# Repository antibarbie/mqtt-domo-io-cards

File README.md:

# mqtt-domo-io-cards
Kicad project for I/O Cards - For DIN RAIL deployment in a domotic "Distribution board"

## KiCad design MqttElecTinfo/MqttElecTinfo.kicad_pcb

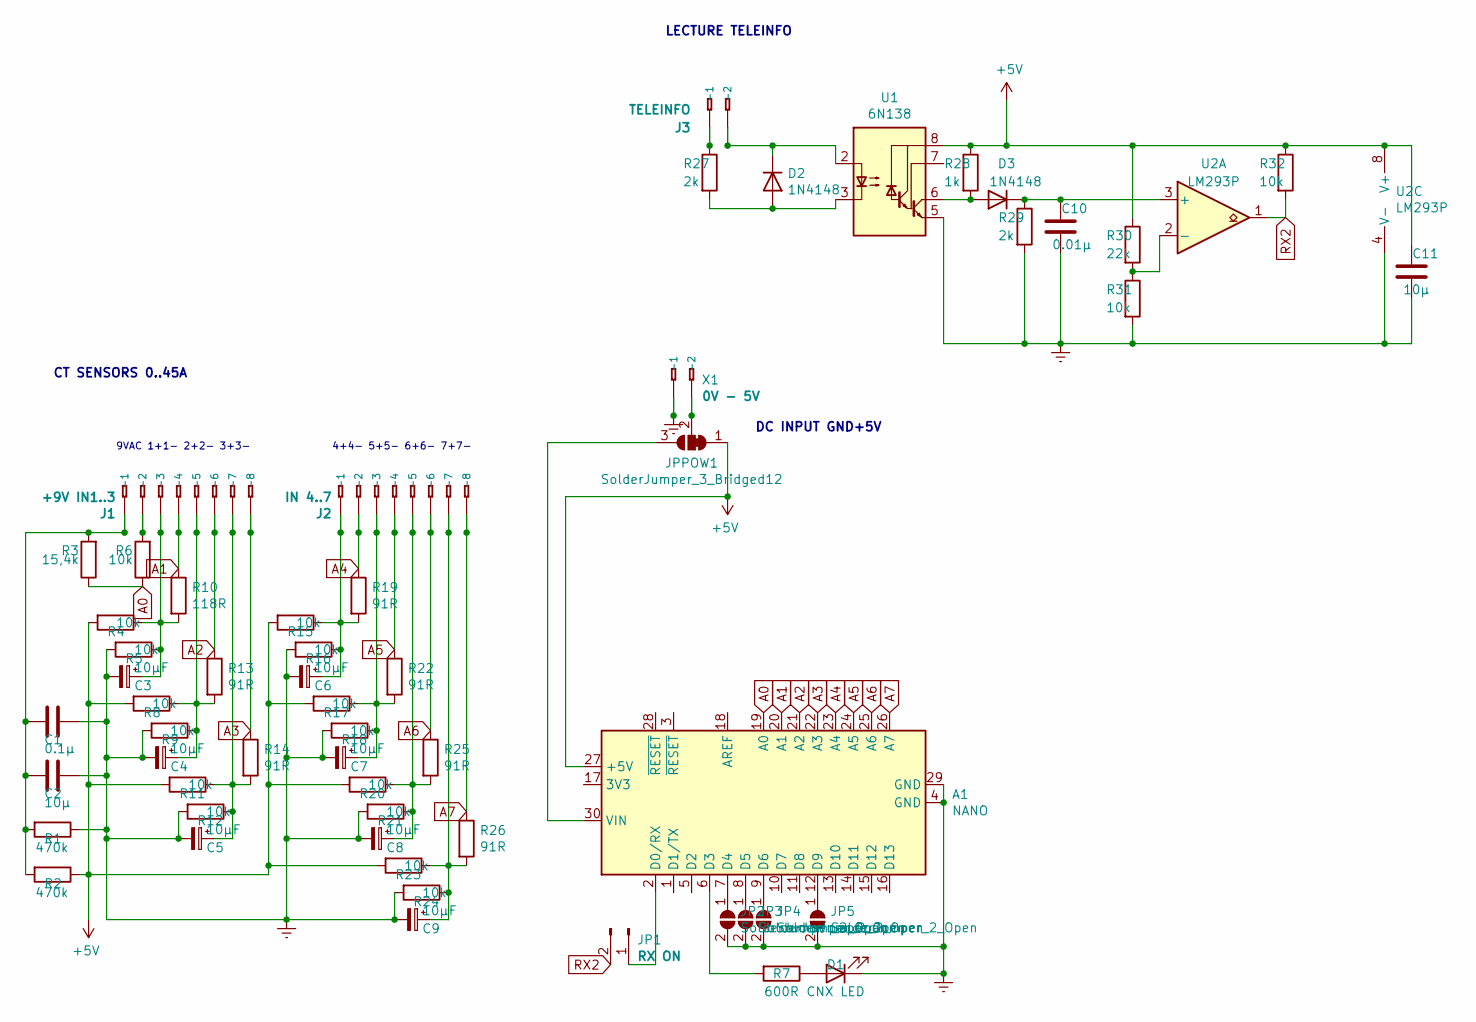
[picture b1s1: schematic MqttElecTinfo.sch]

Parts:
A1: NANO; Arduino_Nano
C1: 0.1µ; CP_Radial_Tantal_D4.5mm_P2.50mm
C2: 10µ; CP_Radial_Tantal_D4.5mm_P5.00mm
C3, C4, C5, C6, C7, C8, C9: 10µF; CP_Radial_D5.0mm_P2.50mm
C10: 0.01µ; CP_Radial_Tantal_D5.0mm_P2.50mm
C11: 10µ; CP_Radial_Tantal_D5.0mm_P5.00mm
D1: CNX LED; LED_D3.0mm
D2, D3: 1N4148; D_DO-35_SOD27_P7.62mm_Horizontal
J1: +9V IN1..3; 233-508; MPN 0233-0508
J2: IN 4..7; 233-508; MPN 0233-0508
J3: TELEINFO; 233-502; MPN 0233-0508
JP1: RX ON; PinHeader_1x02_P2.54mm_Vertical
JP2, JP3, JP4, JP5: SolderJumper_2_Open; SolderJumper-2_P1.3mm_Open_Pad1.0x1.5mm
JPPOW1: SolderJumper_3_Bridged12; SolderJumper-3_P1.3mm_Bridged2Bar12_Pad1.0x1.5mm_NumberLabe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
R1, R2: 470k; R_Axial_DIN0207_L6.3mm_D2.5mm_P2.54mm_Vertical
R3: 15,4k; R_Axial_DIN0207_L6.3mm_D2.5mm_P2.54mm_Vertical
R4, R5, R6, R8, R9, R11, R12, R15, R16, R17, R18, R20, R21, R23, R24, R31, R32: 10k; R_Axial_DIN0207_L6.3mm_D2.5mm_P2.54mm_Vertical
R7: 600R; R_Axial_DIN0207_L6.3mm_D2.5mm_P7.62mm_Horizontal
R10: 118R; R_Axial_DIN0207_L6.3mm_D2.5mm_P2.54mm_Vertical
R13, R14, R19, R22, R25, R26: 91R; R_Axial_DIN0207_L6.3mm_D2.5mm_P2.54mm_Vertical
R27, R29: 2k; R_Axial_DIN0207_L6.3mm_D2.5mm_P2.54mm_Vertical
R28: 1k; R_Axial_DIN0207_L6.3mm_D2.5mm_P2.54mm_Vertical
R30: 22k; R_Axial_DIN0207_L6.3mm_D2.5mm_P2.54mm_Vertical
U1: 6N138; DIP-8_W7.62mm_LongPads
U2: LM293P; DIP-8_W7.62mm_LongPads
X1: 0V - 5V; 233-502; MPN 233-502

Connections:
+5V: A1.27 (+5V), C11.1, JPPOW1.1 (A), R2.1, R4.2, R8.2, R11.2, R15.2, R17.2, R20.2, R23.2, R28.1, R30.1, R32.1, U1.8 (VCC), U2.8 (V+)
A0: A1.19 (A0), R3.1, R6.1
A1: A1.20 (A1), J1.A4 (-4), J1.B4, R10.1
A2: A1.21 (A2), J1.A6 (-6), J1.B6, R13.1
A3: A1.22 (A3), J1.A8 (-8), J1.B8, R14.1
A4: A1.23 (A4), J2.A2 (-2), J2.B2, R19.1
A5: A1.24 (A5), J2.A4 (-4), J2.B4, R22.1
A6: A1.25 (A6), J2.A6 (-6), J2.B6, R25.1
A7: A1.26 (A7), J2.A8 (-8), J2.B8, R26.1
Earth: A1.4 (GND), A1.29 (GND), C1.1, C2.1, C3.2, C4.2, C5.2, C6.2, C7.2, C8.2, C9.2, C10.2, C11.2, D1.1 (K), JP2.2 (B), JP3.2 (B), JP4.2 (B), JP5.2 (B), R1.1, R5.2, R9.2, R12.2, R16.2, R18.2, R21.2, R24.2, R29.2, R31.2, U1.5 (GND), U2.4 (V-), X1.A1 (-1), X1.B1
unnamed: A1.2 (D0/RX), JP1.1
unnamed: A1.6 (D3), R7.2
unnamed: A1.7 (D4), JP2.1 (A)
unnamed: A1.8 (D5), JP3.1 (A)
unnamed: A1.9 (D6), JP4.1 (A)
unnamed: A1.12 (D9), JP5.1 (A)
unnamed: A1.30 (VIN), JPPOW1.3 (B)
unnamed: C1.2, C2.2, J1.A1 (-1), J1.B1, R1.2, R2.2, R3.2
unnamed: C3.1, J1.A3 (-3), J1.B3, R4.1, R5.1, R10.2
unnamed: C4.1, J1.A5 (-5), J1.B5, R8.1, R9.1, R13.2
unnamed: C5.1, J1.A7 (-7), J1.B7, R11.1, R12.1, R14.2
unnamed: C6.1, J2.A1 (-1), J2.B1, R15.1, R16.1, R19.2
unnamed: C7.1, J2.A3 (-3), J2.B3, R17.1, R18.1, R22.2
unnamed: C8.1, J2.A5 (-5), J2.B5, R20.1, R21.1, R25.2
unnamed: C9.1, J2.A7 (-7), J2.B7, R23.1, R24.1, R26.2
unnamed: C10.1, D3.1 (K), R29.1, U2.3 (+)
unnamed: D1.2 (A), R7.1
unnamed: D2.1 (K), J3.A2 (-2), J3.B2, U1.2 (C1)
unnamed: D2.2 (A), R27.2, U1.3 (C2)
unnamed: D3.2 (A), R28.2, U1.6 (VO2)
unnamed: J1.A2 (-2), J1.B2, R6.2
unnamed: J3.A1 (-1), J3.B1, R27.1
unnamed: JPPOW1.2 (C), X1.A2 (-2), X1.B2
unnamed: R30.2, R31.1, U2.2 (-)
RX2: JP1.2, R32.2, U2.1

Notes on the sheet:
9VAC 1+1- 2+2- 3+3-
4+4- 5+5- 6+6- 7+7-
LECTURE TELEINFO
CT SENSORS 0..45A
DC INPUT GND+5V

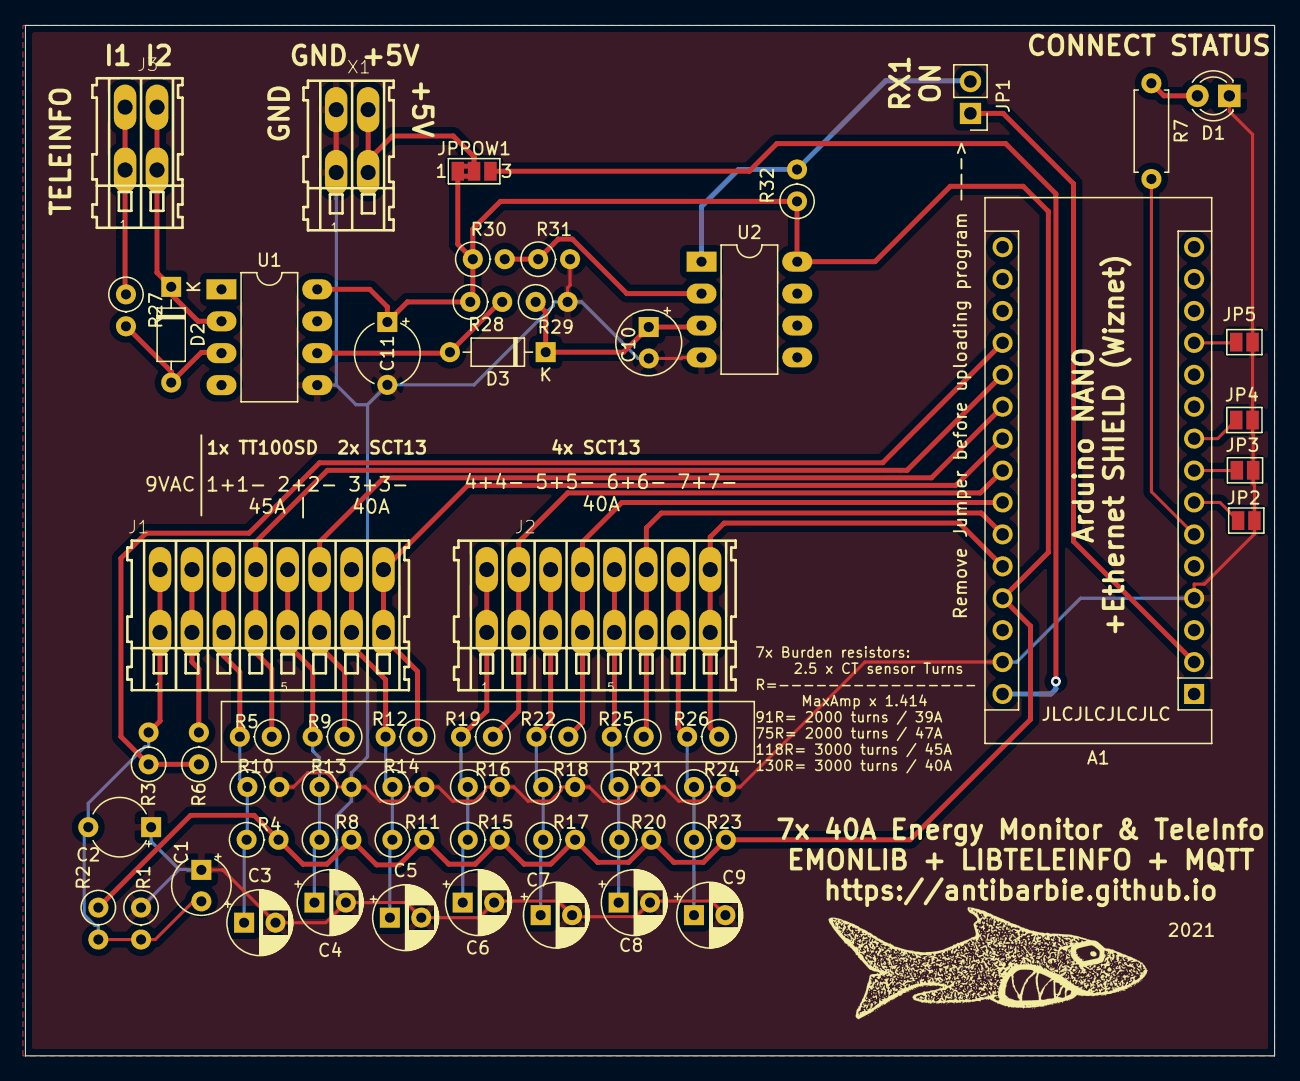
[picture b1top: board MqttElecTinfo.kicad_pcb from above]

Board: 2 copper layers, 99.4 x 82.0 mm, 59 parts (0 on the bottom side), 35 nets.

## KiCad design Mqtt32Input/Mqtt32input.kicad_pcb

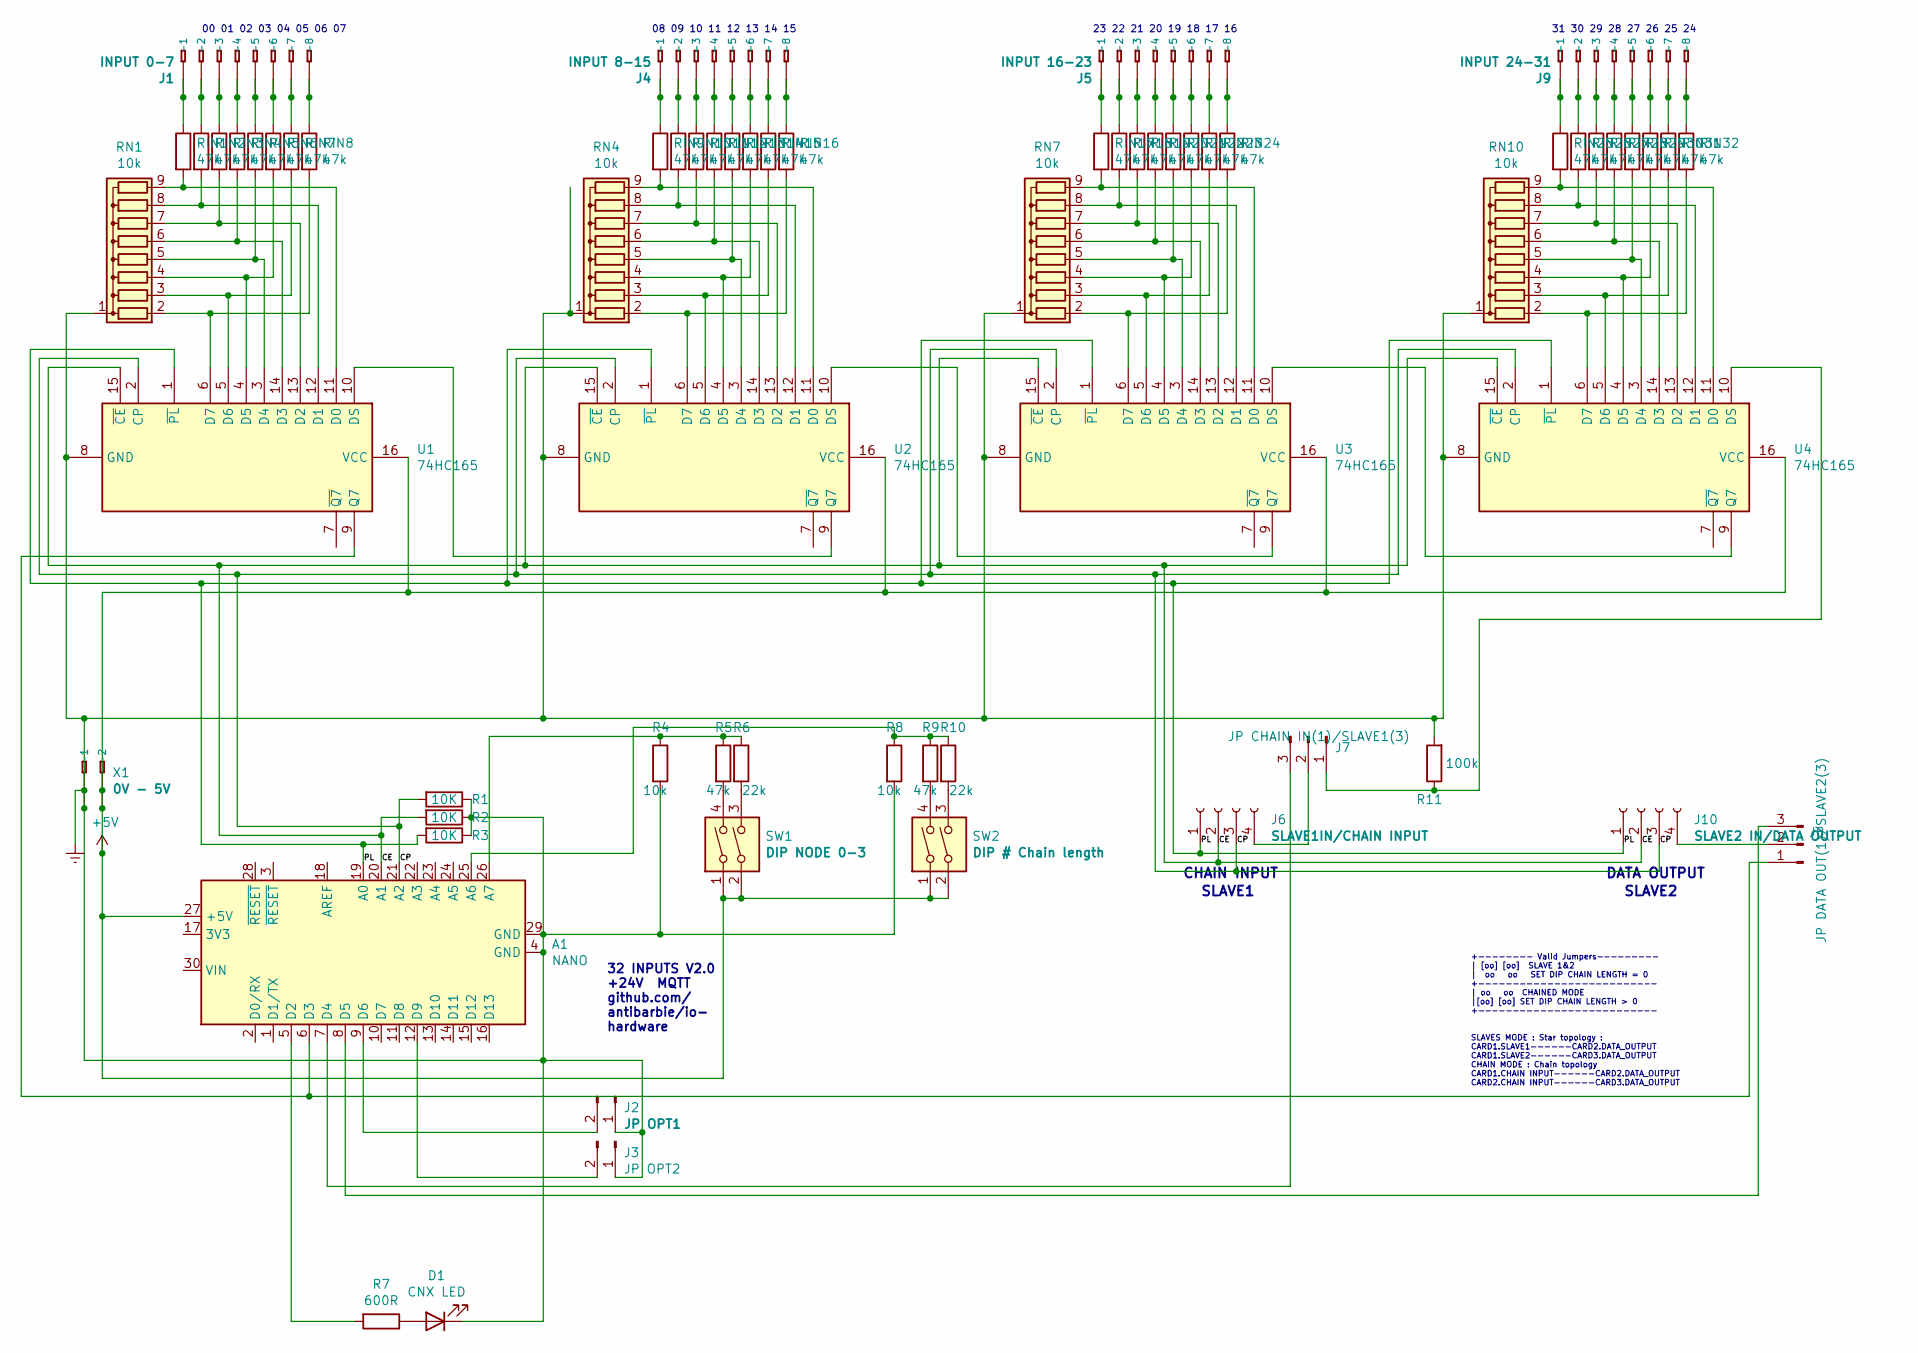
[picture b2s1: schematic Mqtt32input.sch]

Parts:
A1: NANO; Arduino_Nano
D1: CNX LED; LED_D3.0mm
J1: INPUT 0-7; 233-508; MPN 0233-0508
J2: JP OPT1; PinHeader_1x02_P2.54mm_Vertical
J3: JP OPT2; PinHeader_1x02_P2.54mm_Vertical
J4: INPUT 8-15; 233-508; MPN 0233-0508
J5: INPUT 16-23; 233-508; MPN 0233-0508
J6: SLAVE1IN/CHAIN INPUT; PinSocket_1x04_P2.54mm_Vertical
J7: JP CHAIN IN(1)/SLAVE1(3); PinHeader_1x03_P2.54mm_Vertical
J8: JP DATA OUT(1)/SLAVE2(3); PinHeader_1x03_P2.54mm_Vertical
J9: INPUT 24-31; 233-508; MPN 0233-0508
J10: SLAVE2 IN/DATA OUTPUT; PinSocket_1x04_P2.54mm_Vertical
R1, R2, R3: 10K; R_Axial_DIN0207_L6.3mm_D2.5mm_P2.54mm_Vertical
R4, R8: 10k; R_Axial_DIN0207_L6.3mm_D2.5mm_P2.54mm_Vertical
R5, R9: 47k; R_Axial_DIN0207_L6.3mm_D2.5mm_P2.54mm_Vertical
R6, R10: 22k; R_Axial_DIN0207_L6.3mm_D2.5mm_P2.54mm_Vertical
R7: 600R; R_Axial_DIN0207_L6.3mm_D2.5mm_P7.62mm_Horizontal
R11: 100k; R_Axial_DIN0207_L6.3mm_D2.5mm_P2.54mm_Vertical
RIN1, RIN2, RIN3, RIN4, RIN5, RIN6, RIN7, RIN8, RIN9, RIN10, RIN11, RIN12, RIN13, RIN14, RIN15, RIN16, RIN17, RIN18, RIN19, RIN20, RIN21, RIN22, RIN23, RIN24, RIN25, RIN26, RIN27, RIN28, RIN29, RIN30, RIN31, RIN32: 47k; R_Axial_DIN0207_L6.3mm_D2.5mm_P2.54mm_Vertical
RN1, RN4, RN7, RN10: 10k; R_Array_SIP9
SW1: DIP NODE 0-3; SW_DIP_SPSTx02_Slide_9.78x7.26mm_W7.62mm_P2.54mm
SW2: DIP # Chain length; SW_DIP_SPSTx02_Slide_9.78x7.26mm_W7.62mm_P2.54mm
U1, U2, U3, U4: 74HC165; DIP-16_W7.62mm_Socket
X1: 0V - 5V; 233-502; MPN 233-502

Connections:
+5V: A1.27 (+5V), SW1.1, SW1.2, SW2.1, SW2.2, U1.16 (VCC), U2.16 (VCC), U3.16 (VCC), U4.16 (VCC), X1.A2 (-2), X1.B2
/CE: A1.20 (A1), J6.2, J10.2, R2.2, U1.15 (~CE), U2.15 (~CE), U3.15 (~CE), U4.15 (~CE)
/CP: A1.21 (A2), J6.3, J10.3, R1.2, U1.2 (CP), U2.2 (CP), U3.2 (CP), U4.2 (CP)
/PL: A1.19 (A0), J6.1, J10.1, R3.2, U1.1 (~PL), U2.1 (~PL), U3.1 (~PL), U4.1 (~PL)
Earth: A1.4 (GND), A1.29 (GND), D1.1 (K), J2.1, J3.1, R1.1, R2.1, R3.1, R4.2, R8.2, R11.2, RN1.1 (common), RN4.1 (common), RN7.1 (common), RN10.1 (common), U1.8 (GND), U2.8 (GND), U3.8 (GND), U4.8 (GND), X1.A1 (-1), X1.B1
unnamed: A1.5 (D2), R7.2
unnamed: A1.6 (D3), J8.1, U1.9 (Q7)
unnamed: A1.7 (D4), J7.3
unnamed: A1.8 (D5), J8.3
unnamed: A1.9 (D6), J2.2
unnamed: A1.12 (D9), J3.2
unnamed: A1.25 (A6), R8.1, R9.1, R10.1
unnamed: A1.26 (A7), R4.1, R5.1, R6.1
unnamed: D1.2 (A), R7.1
unnamed: J1.A1 (-1), J1.B1, RIN1.1
unnamed: J1.A2 (-2), J1.B2, RIN2.1
unnamed: J1.A3 (-3), J1.B3, RIN3.1
unnamed: J1.A4 (-4), J1.B4, RIN4.1
unnamed: J1.A5 (-5), J1.B5, RIN5.1
unnamed: J1.A6 (-6), J1.B6, RIN6.1
unnamed: J1.A7 (-7), J1.B7, RIN7.1
unnamed: J1.A8 (-8), J1.B8, RIN8.1
unnamed: J4.A1 (-1), J4.B1, RIN9.1
unnamed: J4.A2 (-2), J4.B2, RIN10.1
unnamed: J4.A3 (-3), J4.B3, RIN11.1
unnamed: J4.A4 (-4), J4.B4, RIN12.1
unnamed: J4.A5 (-5), J4.B5, RIN13.1
unnamed: J4.A6 (-6), J4.B6, RIN14.1
unnamed: J4.A7 (-7), J4.B7, RIN15.1
unnamed: J4.A8 (-8), J4.B8, RIN16.1
unnamed: J5.A1 (-1), J5.B1, RIN17.1
unnamed: J5.A2 (-2), J5.B2, RIN18.1
unnamed: J5.A3 (-3), J5.B3, RIN19.1
unnamed: J5.A4 (-4), J5.B4, RIN20.1
unnamed: J5.A5 (-5), J5.B5, RIN21.1
unnamed: J5.A6 (-6), J5.B6, RIN22.1
unnamed: J5.A7 (-7), J5.B7, RIN23.1
unnamed: J5.A8 (-8), J5.B8, RIN24.1
unnamed: J6.4, J7.2
unnamed: J7.1, R11.1, U4.10 (DS)
unnamed: J9.A1 (-1), J9.B1, RIN25.1
unnamed: J9.A2 (-2), J9.B2, RIN26.1
unnamed: J9.A3 (-3), J9.B3, RIN27.1
unnamed: J9.A4 (-4), J9.B4, RIN28.1
unnamed: J9.A5 (-5), J9.B5, RIN29.1
unnamed: J9.A6 (-6), J9.B6, RIN30.1
unnamed: J9.A7 (-7), J9.B7, RIN31.1
unnamed: J9.A8 (-8), J9.B8, RIN32.1
unnamed: J8.2, J10.4
unnamed: R5.2, SW1.4
unnamed: R6.2, SW1.3
unnamed: R9.2, SW2.4
unnamed: R10.2, SW2.3
unnamed: RIN1.2, RN1.9 (R8), U1.11 (D0)
unnamed: RIN2.2, RN1.8 (R7), U1.12 (D1)
unnamed: RIN3.2, RN1.7 (R6), U1.13 (D2)
unnamed: RIN4.2, RN1.6 (R5), U1.14 (D3)
unnamed: RIN5.2, RN1.5 (R4), U1.3 (D4)
unnamed: RIN6.2, RN1.4 (R3), U1.4 (D5)
unnamed: RIN7.2, RN1.3 (R2), U1.5 (D6)
unnamed: RIN8.2, RN1.2 (R1), U1.6 (D7)
unnamed: RIN9.2, RN4.9 (R8), U2.11 (D0)
unnamed: RIN10.2, RN4.8 (R7), U2.12 (D1)
unnamed: RIN11.2, RN4.7 (R6), U2.13 (D2)
unnamed: RIN12.2, RN4.6 (R5), U2.14 (D3)
unnamed: RIN13.2, RN4.5 (R4), U2.3 (D4)
unnamed: RIN14.2, RN4.4 (R3), U2.4 (D5)
unnamed: RIN15.2, RN4.3 (R2), U2.5 (D6)
unnamed: RIN16.2, RN4.2 (R1), U2.6 (D7)
unnamed: RIN17.2, RN7.9 (R8), U3.11 (D0)
unnamed: RIN18.2, RN7.8 (R7), U3.12 (D1)
unnamed: RIN19.2, RN7.7 (R6), U3.13 (D2)
unnamed: RIN20.2, RN7.6 (R5), U3.14 (D3)
unnamed: RIN21.2, RN7.5 (R4), U3.3 (D4)
unnamed: RIN22.2, RN7.4 (R3), U3.4 (D5)
unnamed: RIN23.2, RN7.3 (R2), U3.5 (D6)
unnamed: RIN24.2, RN7.2 (R1), U3.6 (D7)
unnamed: RIN25.2, RN10.9 (R8), U4.11 (D0)
unnamed: RIN26.2, RN10.8 (R7), U4.12 (D1)
unnamed: RIN27.2, RN10.7 (R6), U4.13 (D2)
unnamed: RIN28.2, RN10.6 (R5), U4.14 (D3)
unnamed: RIN29.2, RN10.5 (R4), U4.3 (D4)
unnamed: RIN30.2, RN10.4 (R3), U4.4 (D5)
unnamed: RIN31.2, RN10.3 (R2), U4.5 (D6)
unnamed: RIN32.2, RN10.2 (R1), U4.6 (D7)
unnamed: U1.10 (DS), U2.9 (Q7)
unnamed: U2.10 (DS), U3.9 (Q7)
unnamed: U3.10 (DS), U4.9 (Q7)

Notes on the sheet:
32 INPUTS V2.0 +24V MQTT github.com/ antibarbie/io- hardware
00 01 02 03 04 05 06 07
08 09 10 11 12 13 14 15
23 22 21 20 19 18 17 16
31 30 29 28 27 26 25 24
+-------- Valid Jumpers--------- | [oo] [oo] SLAVE 1&2 | oo oo SET DIP CHAIN LENGTH = 0 +-------------------------- | oo oo CHAINED MODE |[oo] [oo] SET DIP CHAIN LENGTH > 0 +--------------------------
SLAVES MODE : Star topology : CARD1.SLAVE1------CARD2.DATA_OUTPUT CARD1.SLAVE2------CARD3.DATA_OUTPUT CHAIN MODE : Chain topology CARD1.CHAIN INPUT------CARD2.DATA_OUTPUT CARD2.CHAIN INPUT------CARD3.DATA_OUTPUT
SLAVE1
CHAIN INPUT
SLAVE2
DATA OUTPUT

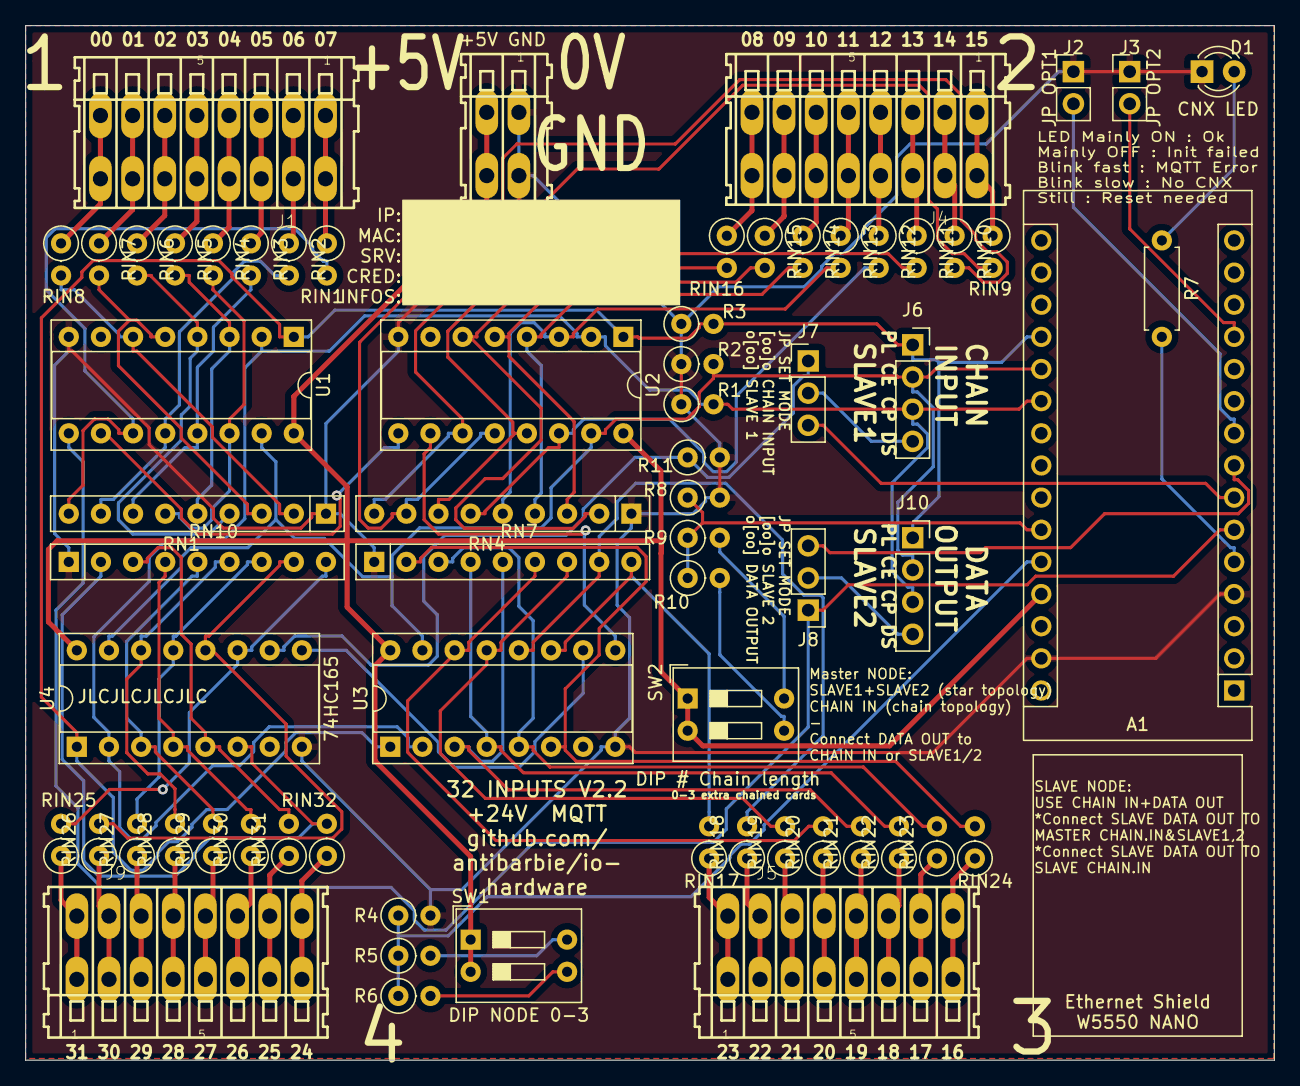
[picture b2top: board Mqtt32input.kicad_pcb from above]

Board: 2 copper layers, 98.7 x 81.7 mm, 66 parts (0 on the bottom side), 88 nets.

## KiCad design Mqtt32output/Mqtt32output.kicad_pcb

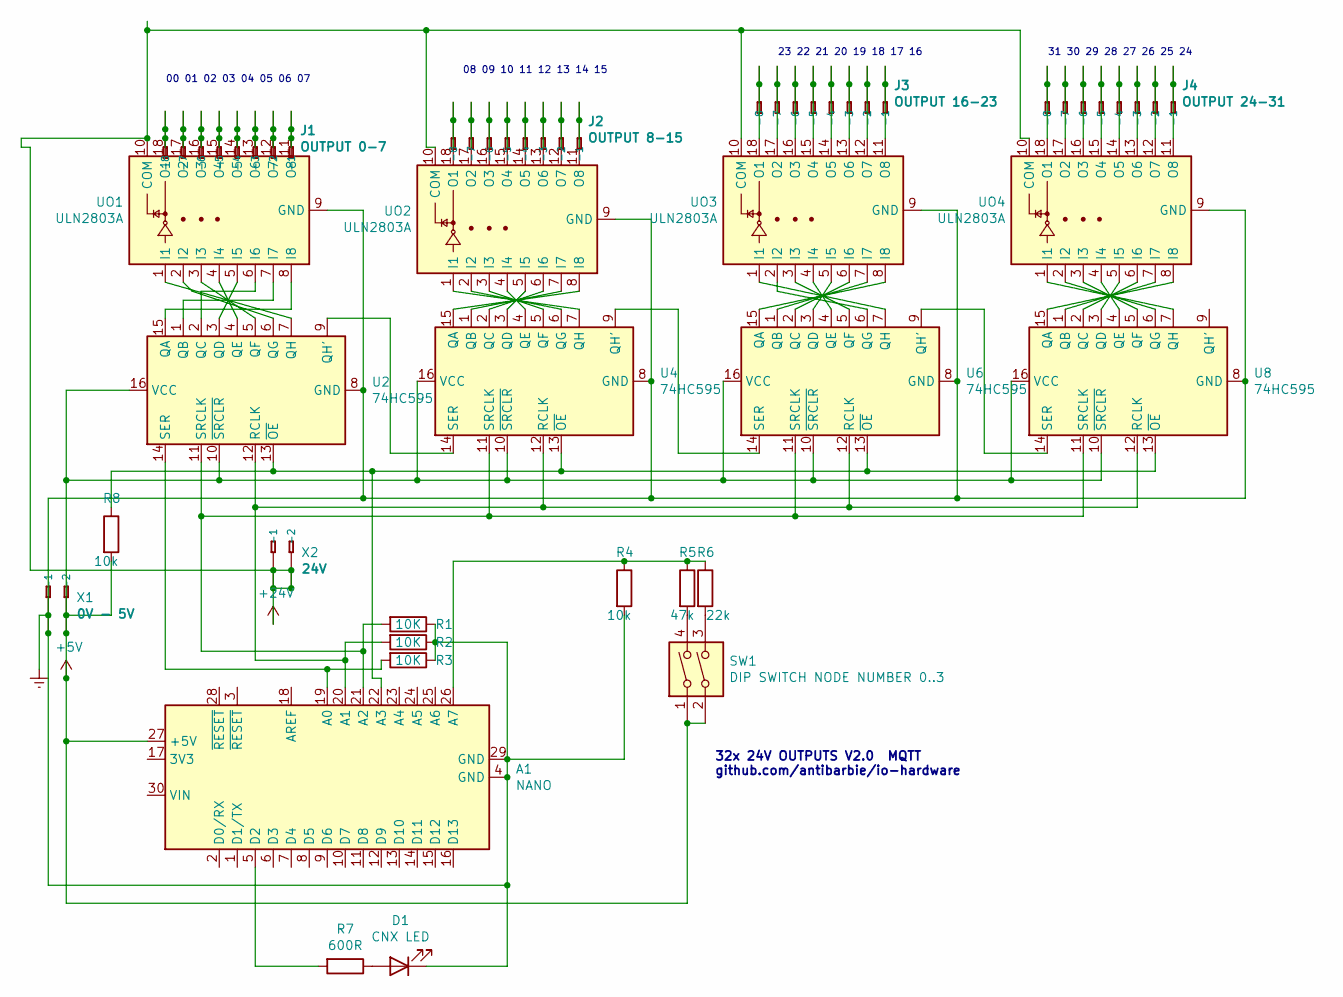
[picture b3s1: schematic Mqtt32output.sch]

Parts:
A1: NANO; Arduino_Nano
D1: CNX LED; LED_D3.0mm
J1: OUTPUT 0-7; 233-508; MPN 0233-0508
J2: OUTPUT 8-15; 233-508; MPN 0233-0508
J3: OUTPUT 16-23; 233-508; MPN 0233-0508
J4: OUTPUT 24-31; 233-508; MPN 0233-0508
R1, R2, R3: 10K; R_Axial_DIN0207_L6.3mm_D2.5mm_P2.54mm_Vertical
R4, R8: 10k; R_Axial_DIN0207_L6.3mm_D2.5mm_P2.54mm_Vertical
R5: 47k; R_Axial_DIN0207_L6.3mm_D2.5mm_P2.54mm_Vertical
R6: 22k; R_Axial_DIN0207_L6.3mm_D2.5mm_P2.54mm_Vertical
R7: 600R; R_Axial_DIN0207_L6.3mm_D2.5mm_P7.62mm_Horizontal
SW1: DIP SWITCH NODE NUMBER 0..3; SW_DIP_SPSTx02_Slide_9.78x7.26mm_W7.62mm_P2.54mm
U2, U4, U6, U8: 74HC595; DIP-16_W7.62mm_Socket
UO1, UO2, UO3, UO4: ULN2803A; DIP-18_W7.62mm_Socket
X1: 0V - 5V; 233-502; MPN 233-502
X2: 24V; 233-502; MPN 233-502

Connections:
+5V: A1.27 (+5V), R8.2, SW1.1, SW1.2, U2.10 (~SRCLR), U2.16 (VCC), U4.10 (~SRCLR), U4.16 (VCC), U6.10 (~SRCLR), U6.16 (VCC), U8.10 (~SRCLR), U8.16 (VCC), X1.A2 (-2), X1.B2
+24V: UO1.10 (COM), UO2.10 (COM), UO3.10 (COM), UO4.10 (COM), X2.A1 (-1), X2.A2 (-2), X2.B1, X2.B2
Earth: A1.4 (GND), A1.29 (GND), D1.1 (K), R1.1, R2.1, R3.1, R4.2, U2.8 (GND), U4.8 (GND), U6.8 (GND), U8.8 (GND), UO1.9 (GND), UO2.9 (GND), UO3.9 (GND), UO4.9 (GND), X1.A1 (-1), X1.B1
unnamed: A1.5 (D2), R7.2
unnamed: A1.19 (A0), R3.2, U2.14 (SER)
unnamed: A1.20 (A1), R2.2, U2.12 (RCLK), U4.12 (RCLK), U6.12 (RCLK), U8.12 (RCLK)
unnamed: A1.21 (A2), R1.2, U2.11 (SRCLK), U4.11 (SRCLK), U6.11 (SRCLK), U8.11 (SRCLK)
unnamed: A1.22 (A3), R8.1, U2.13 (~OE), U4.13 (~OE), U6.13 (~OE), U8.13 (~OE)
unnamed: A1.26 (A7), R4.1, R5.1, R6.1
unnamed: D1.2 (A), R7.1
unnamed: J1.A1 (-1), J1.B1, UO1.11 (O8)
unnamed: J1.A2 (-2), J1.B2, UO1.12 (O7)
unnamed: J1.A3 (-3), J1.B3, UO1.13 (O6)
unnamed: J1.A4 (-4), J1.B4, UO1.14 (O5)
unnamed: J1.A5 (-5), J1.B5, UO1.15 (O4)
unnamed: J1.A6 (-6), J1.B6, UO1.16 (O3)
unnamed: J1.A7 (-7), J1.B7, UO1.17 (O2)
unnamed: J1.A8 (-8), J1.B8, UO1.18 (O1)
unnamed: J2.A1 (-1), J2.B1, UO2.11 (O8)
unnamed: J2.A2 (-2), J2.B2, UO2.12 (O7)
unnamed: J2.A3 (-3), J2.B3, UO2.13 (O6)
unnamed: J2.A4 (-4), J2.B4, UO2.14 (O5)
unnamed: J2.A5 (-5), J2.B5, UO2.15 (O4)
unnamed: J2.A6 (-6), J2.B6, UO2.16 (O3)
unnamed: J2.A7 (-7), J2.B7, UO2.17 (O2)
unnamed: J2.A8 (-8), J2.B8, UO2.18 (O1)
unnamed: J3.A1 (-1), J3.B1, UO3.11 (O8)
unnamed: J3.A2 (-2), J3.B2, UO3.12 (O7)
unnamed: J3.A3 (-3), J3.B3, UO3.13 (O6)
unnamed: J3.A4 (-4), J3.B4, UO3.14 (O5)
unnamed: J3.A5 (-5), J3.B5, UO3.15 (O4)
unnamed: J3.A6 (-6), J3.B6, UO3.16 (O3)
unnamed: J3.A7 (-7), J3.B7, UO3.17 (O2)
unnamed: J3.A8 (-8), J3.B8, UO3.18 (O1)
unnamed: J4.A1 (-1), J4.B1, UO4.11 (O8)
unnamed: J4.A2 (-2), J4.B2, UO4.12 (O7)
unnamed: J4.A3 (-3), J4.B3, UO4.13 (O6)
unnamed: J4.A4 (-4), J4.B4, UO4.14 (O5)
unnamed: J4.A5 (-5), J4.B5, UO4.15 (O4)
unnamed: J4.A6 (-6), J4.B6, UO4.16 (O3)
unnamed: J4.A7 (-7), J4.B7, UO4.17 (O2)
unnamed: J4.A8 (-8), J4.B8, UO4.18 (O1)
unnamed: R5.2, SW1.4
unnamed: R6.2, SW1.3
unnamed: U2.1 (QB), UO1.7 (I7)
unnamed: U2.2 (QC), UO1.6 (I6)
unnamed: U2.3 (QD), UO1.5 (I5)
unnamed: U2.4 (QE), UO1.4 (I4)
unnamed: U2.5 (QF), UO1.3 (I3)
unnamed: U2.6 (QG), UO1.2 (I2)
unnamed: U2.7 (QH), UO1.1 (I1)
unnamed: U2.9 (QH'), U4.14 (SER)
unnamed: U2.15 (QA), UO1.8 (I8)
unnamed: U4.1 (QB), UO2.7 (I7)
unnamed: U4.2 (QC), UO2.6 (I6)
unnamed: U4.3 (QD), UO2.5 (I5)
unnamed: U4.4 (QE), UO2.4 (I4)
unnamed: U4.5 (QF), UO2.3 (I3)
unnamed: U4.6 (QG), UO2.2 (I2)
unnamed: U4.7 (QH), UO2.1 (I1)
unnamed: U4.9 (QH'), U6.14 (SER)
unnamed: U4.15 (QA), UO2.8 (I8)
unnamed: U6.1 (QB), UO3.7 (I7)
unnamed: U6.2 (QC), UO3.6 (I6)
unnamed: U6.3 (QD), UO3.5 (I5)
unnamed: U6.4 (QE), UO3.4 (I4)
unnamed: U6.5 (QF), UO3.3 (I3)
unnamed: U6.6 (QG), UO3.2 (I2)
unnamed: U6.7 (QH), UO3.1 (I1)
unnamed: U6.9 (QH'), U8.14 (SER)
unnamed: U6.15 (QA), UO3.8 (I8)
unnamed: U8.1 (QB), UO4.7 (I7)
unnamed: U8.2 (QC), UO4.6 (I6)
unnamed: U8.3 (QD), UO4.5 (I5)
unnamed: U8.4 (QE), UO4.4 (I4)
unnamed: U8.5 (QF), UO4.3 (I3)
unnamed: U8.6 (QG), UO4.2 (I2)
unnamed: U8.7 (QH), UO4.1 (I1)
unnamed: U8.15 (QA), UO4.8 (I8)

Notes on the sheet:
32x 24V OUTPUTS V2.0 MQTT github.com/antibarbie/io-hardware
00 01 02 03 04 05 06 07
08 09 10 11 12 13 14 15
23 22 21 20 19 18 17 16
31 30 29 28 27 26 25 24

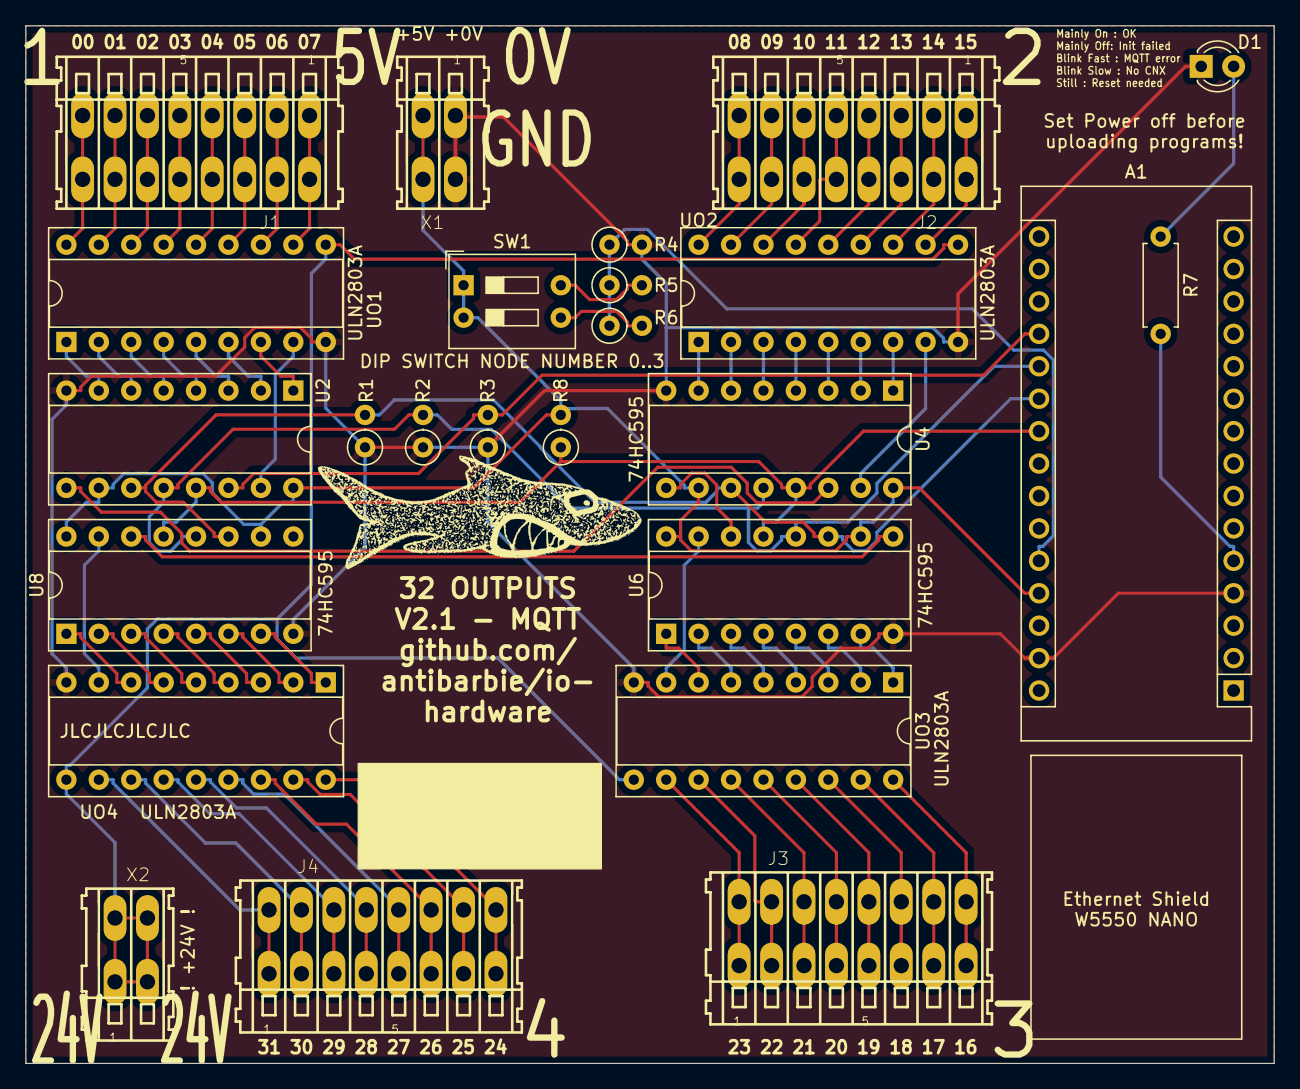
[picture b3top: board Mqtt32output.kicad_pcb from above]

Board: 2 copper layers, 97.8 x 81.3 mm, 25 parts (0 on the bottom side), 79 nets.

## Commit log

2020-11-29 Initial release
2021-01-18 Fix component placement, and GND connexion + board size on inputs
2021-01-18 Revision with through hole resistor, more robust that SMD Array
2021-10-24 Fix comments/layout on the main schematics
2021-11-07 Add Arduino NANO board for MQTT+Emonlib+LibTeleinfo
